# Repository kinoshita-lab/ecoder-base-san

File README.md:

# Encoder Base San

[Document in Japanese](README_ja.md)
Encoder Base San is a utility PCB for using Rotary Encoder.
Dedicated to fit widely used 12mm size encoders such as Alps Alpine's EC12E2420801 and its compatibles.

It implements filter circuit shown on [ALPS ALPINE WEBSITE](https://tech.alpsalpine.com/e/products/detail/EC12E2420801/) and pull-up registor for switch output. Please see schematics for details.

## Kit Contents

- Circuit board
- 1x5 pin header
(Important: This kit does not include rotary encoder itself. Please use with you own rotary encoder).

## How to assemble

1. Solder pin header and rotary encoder.

## Application

1x5 area can solder other connectors, directions. For example you can use pin socket, solder pin header from top side, etc., according to your demand.

It has four screw holes. They can be used for fixing, for example, when strong force is applied.

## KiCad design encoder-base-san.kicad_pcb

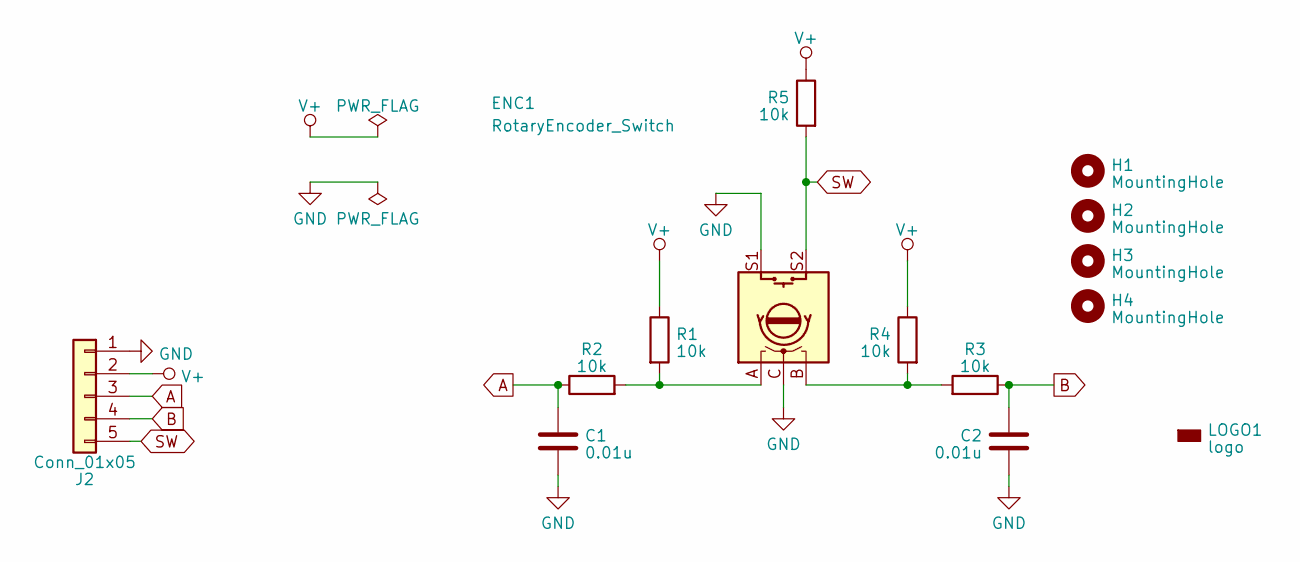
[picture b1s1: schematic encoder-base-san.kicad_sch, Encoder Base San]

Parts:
C1, C2: 0.01u; C_0402_1005Metric_Pad0.74x0.62mm_HandSolder; LCSC C2840480
ENC1: RotaryEncoder_Switch; RotaryEncoder_Alps_12_with_switch
H1, H2, H3, H4: MountingHole; MountingHole_3.2mm_M3
J2: Conn_01x05; PinHeader_1x05_P2.54mm_Vertical
LOGO1: logo; kinoshita-logo_simplified_600dpi
R1, R2, R3, R4, R5: 10k; C_0402_1005Metric_Pad0.74x0.62mm_HandSolder; LCSC C25744

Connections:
A: C1.1, J2.3, R2.1
B: C2.1, J2.4, R3.1
GND: C1.2, C2.2, ENC1.C, ENC1.S1, J2.1
unnamed: ENC1.A, R1.2, R2.2
unnamed: ENC1.B, R3.2, R4.2
SW: ENC1.S2, J2.5, R5.2
VCC1: J2.2, R1.1, R4.1, R5.1

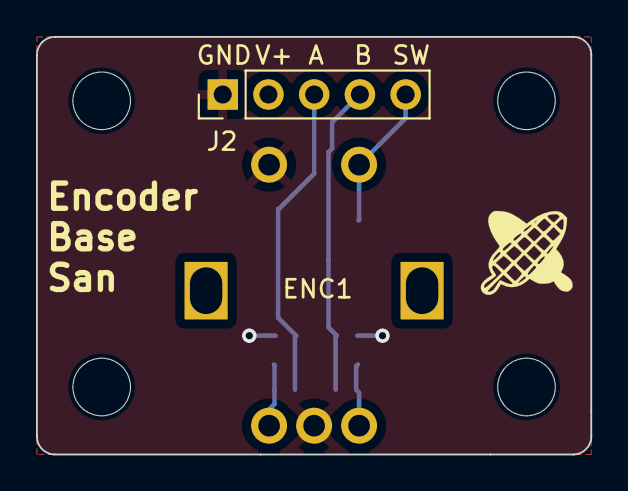
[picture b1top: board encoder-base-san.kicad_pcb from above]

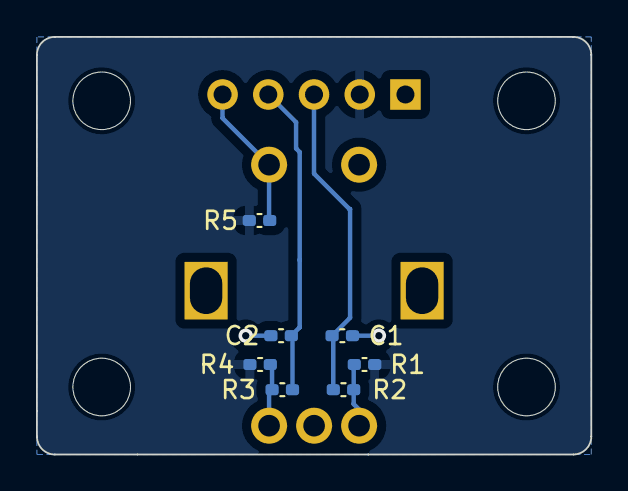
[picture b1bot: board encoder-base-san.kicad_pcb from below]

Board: 2 copper layers, 30.8 x 23.2 mm, 14 parts (7 on the bottom side), 7 nets.

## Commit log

2023-11-19 add files, docs
2023-11-19 add docs
2023-11-19 modify docs
